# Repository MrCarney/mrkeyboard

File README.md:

# MrKeyboard

## Description
Ergogen 4.x generated low-profile backlit split keyboard with hot-swappable choc switches and per-key RGB LEDs.

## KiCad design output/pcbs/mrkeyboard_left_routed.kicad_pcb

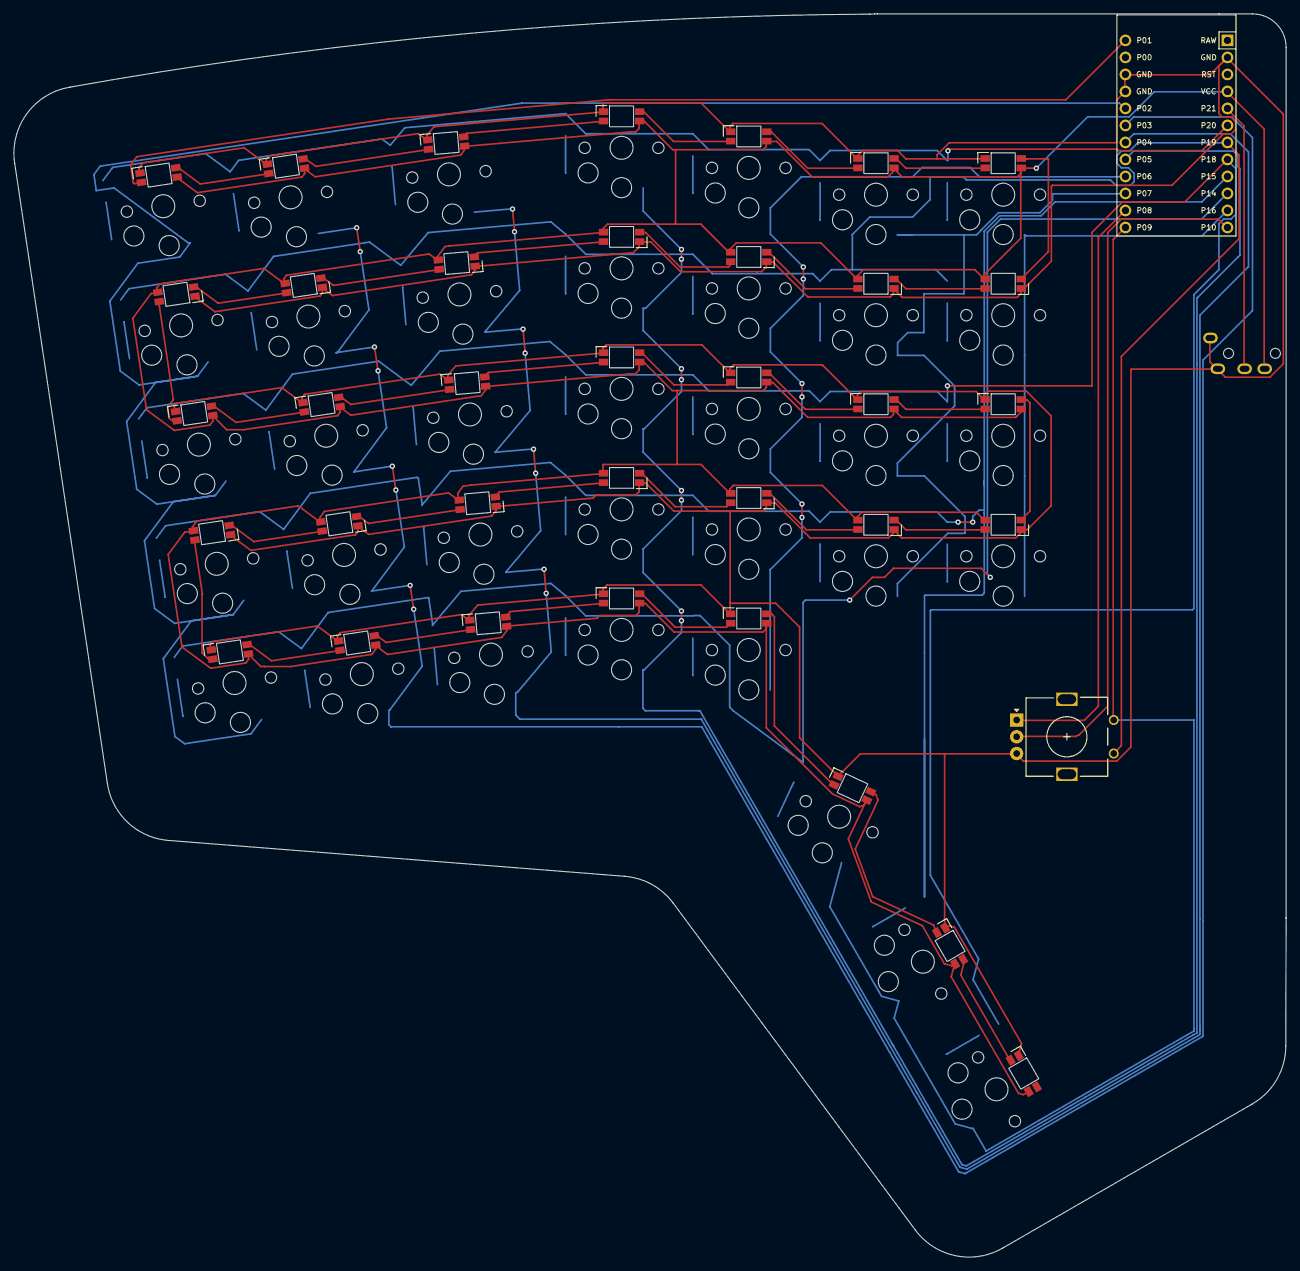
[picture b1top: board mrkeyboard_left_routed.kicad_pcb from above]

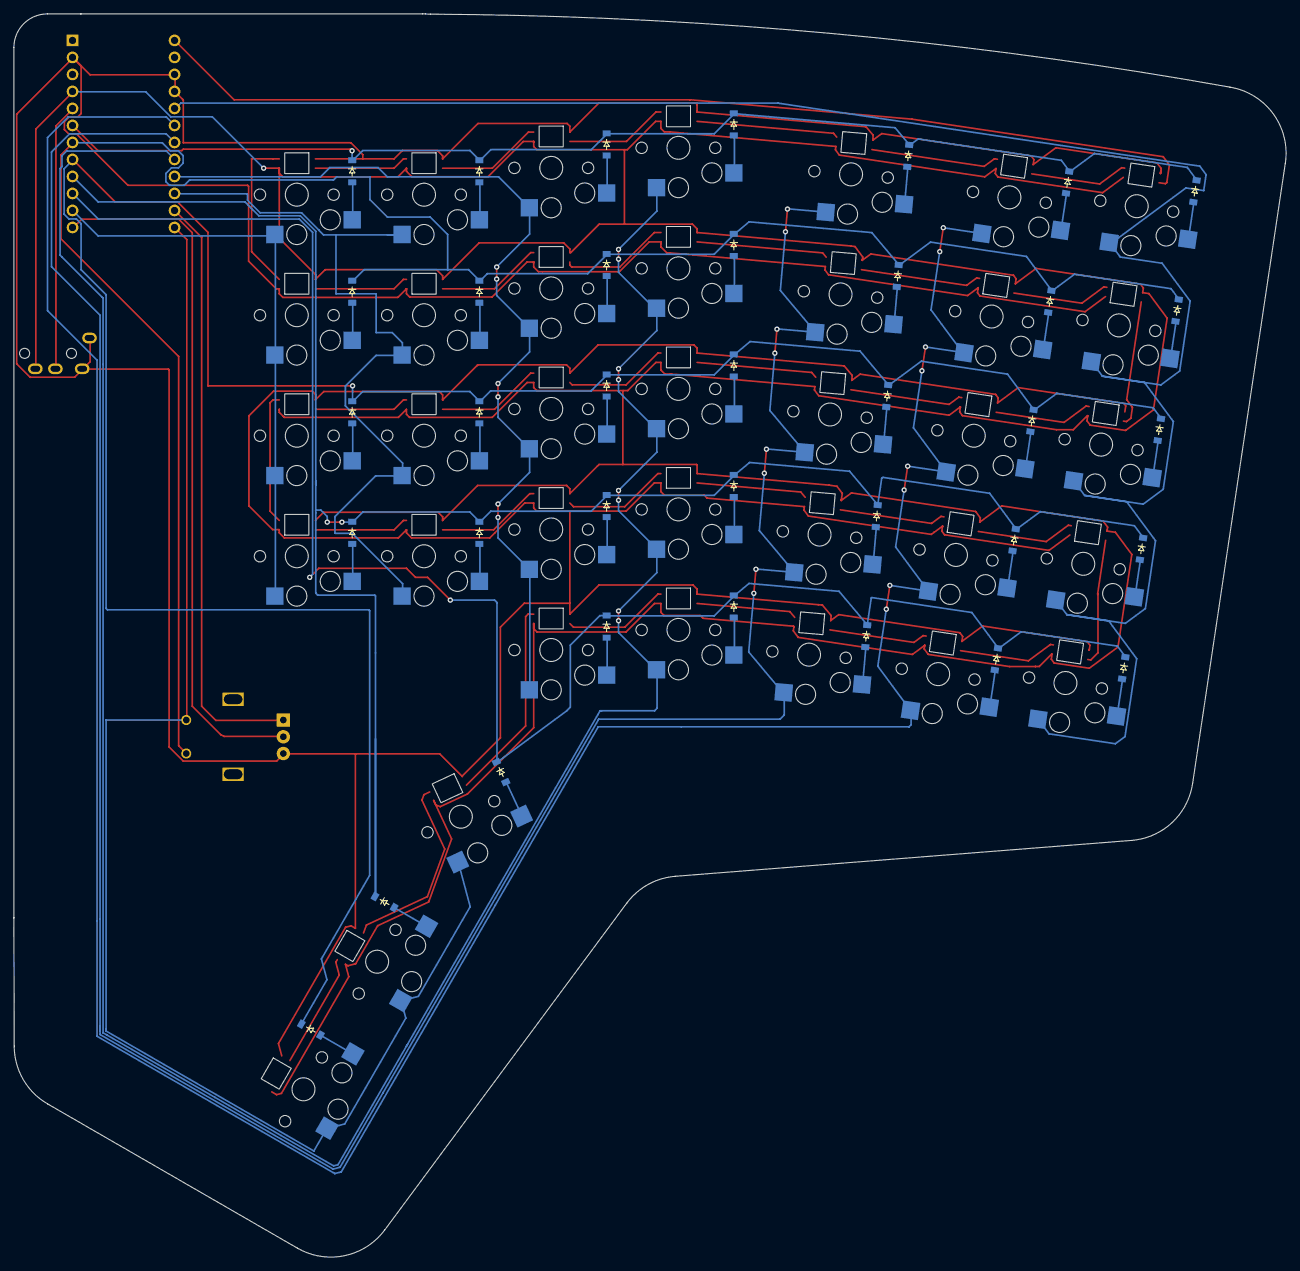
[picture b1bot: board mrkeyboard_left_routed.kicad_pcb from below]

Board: 2 copper layers, 190.0 x 185.7 mm, 111 parts (36 on the bottom side), 90 nets.

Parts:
D1, D2, D3, D4, D5, D6, D7, D8, D9, D10, D11, D12, D13, D14, D15, D16, D17, D18, D19, D20, D21, D22, D23, D24, D25, D26, D27, D28, D29, D30, D31, D32, D33, D34, D35, D36: ComboDiode
LED1, LED2, LED3, LED4, LED5, LED6, LED7, LED8, LED9, LED10, LED11, LED12, LED13, LED14, LED15, LED16, LED17, LED18, LED19, LED20, LED21, LED22, LED23, LED24, LED25, LED26, LED27, LED28, LED29, LED30, LED31, LED32, LED33, LED34, LED35, LED36: led_SK6812mini-e (underglowsingle-side)
MCU1: ProMicro
ROT1: rotary_encoder
S1, S2, S3, S4, S5, S6, S7, S8, S9, S10, S11, S12, S13, S14, S15, S16, S17, S18, S19, S20, S21, S22, S23, S24, S25, S26, S27, S28, S29, S30, S31, S32, S33, S34, S35, S36: PG1350
TRRS1: TRRS-PJ-320A-dual

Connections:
GND: LED1.3, LED2.3, LED3.3, LED4.3, LED5.3, LED6.3, LED7.3, LED8.3, LED9.3, LED10.3, LED11.3, LED12.3, LED13.3, LED14.3, LED15.3, LED16.3, LED17.3, LED18.3, LED19.3, LED20.3, LED21.3, LED22.3, LED23.3, LED24.3, LED25.3, LED26.3, LED27.3, LED28.3, LED29.3, LED30.3, LED31.3, LED32.3, LED33.3, LED34.3, LED35.3, LED36.3, MCU1.2, MCU1.15, MCU1.16, ROT1.B, TRRS1.1, TRRS1.2
L0102: LED5.2, LED10.4
L0203: LED10.2, LED15.4
L0304: LED15.2, LED20.4
L0405: LED20.2, LED25.4
L0506: LED25.2, LED29.4
L0607: LED29.2, LED33.4
L0714: LED32.4, LED33.2
L0815: LED3.4, LED4.2
L0908: LED4.4, LED9.2
L1009: LED9.4, LED14.2
L1110: LED14.4, LED19.2
L1211: LED19.4, LED24.2
L1312: LED24.4, LED28.2
L1413: LED28.4, LED32.2
L1516: LED3.2, LED8.4
L1617: LED8.2, LED13.4
L1718: LED13.2, LED18.4
L1819: LED18.2, LED23.4
L1920: LED23.2, LED27.4
L2021: LED27.2, LED31.4
L2128: LED30.4, LED31.2
L2229: LED1.4, LED2.2
L2322: LED2.4, LED7.2
L2423: LED7.4, LED12.2
L2524: LED12.4, LED17.2
L2625: LED17.4, LED22.2
L2726: LED22.4, LED26.2
L2827: LED26.4, LED30.2
L2930: LED1.2, LED6.4
L3031: LED6.2, LED11.4
L3132: LED11.2, LED16.4
L3233: LED16.2, LED21.4
L3334: LED21.2, LED34.4
L3435: LED34.2, LED35.4
L3536: LED35.2, LED36.4
P1: LED5.4, MCU1.13
P2: MCU1.17, S1.1, S2.1, S3.1, S4.1, S5.1
P3: MCU1.18, S6.1, S7.1, S8.1, S9.1, S10.1
P4: MCU1.19, S11.1, S12.1, S13.1, S14.1, S15.1
P5: MCU1.20, S16.1, S17.1, S18.1, S19.1, S20.1
P6: MCU1.21, S21.1, S22.1, S23.1, S24.1, S25.1
P7: MCU1.22, S26.1, S27.1, S28.1, S29.1
P8: MCU1.23, ROT1.A
P9: MCU1.24, ROT1.1, S34.1, S35.1, S36.1
P10: MCU1.12, ROT1.C
P14: D1.1, D6.1, D11.1, D16.1, D21.1, D34.1, MCU1.10
P15: D2.1, D7.1, D12.1, D17.1, D22.1, D26.1, D30.1, D35.1, MCU1.9
P16: MCU1.11, S30.1, S31.1, S32.1, S33.1
P18: D3.1, D8.1, D13.1, D18.1, D23.1, D27.1, D31.1, D36.1, MCU1.8
P19: D4.1, D9.1, D14.1, D19.1, D24.1, D28.1, D32.1, MCU1.7, ROT1.2
P20: D5.1, D10.1, D15.1, D20.1, D25.1, D29.1, D33.1, MCU1.6
P21: MCU1.5, TRRS1.3
VCC: LED1.1, LED2.1, LED3.1, LED4.1, LED5.1, LED6.1, LED7.1, LED8.1, LED9.1, LED10.1, LED11.1, LED12.1, LED13.1, LED14.1, LED15.1, LED16.1, LED17.1, LED18.1, LED19.1, LED20.1, LED21.1, LED22.1, LED23.1, LED24.1, LED25.1, LED26.1, LED27.1, LED28.1, LED29.1, LED30.1, LED31.1, LED32.1, LED33.1, LED34.1, LED35.1, LED36.1, MCU1.4, TRRS1.4
far_arrows: D1.2, S1.2
far_bottom: D2.2, S2.2
far_home: D3.2, S3.2
far_number: D5.2, S5.2
far_top: D4.2, S4.2
index_arrows: D21.2, S21.2
index_bottom: D22.2, S22.2
index_home: D23.2, S23.2
index_number: D25.2, S25.2
index_top: D24.2, S24.2
indexplus_bottom: D26.2, S26.2
indexplus_home: D27.2, S27.2
indexplus_number: D29.2, S29.2
indexplus_top: D28.2, S28.2
inside_bottom: D30.2, S30.2
inside_home: D31.2, S31.2
inside_number: D33.2, S33.2
inside_top: D32.2, S32.2
middle_arrows: D16.2, S16.2
middle_bottom: D17.2, S17.2
middle_home: D18.2, S18.2
middle_number: D20.2, S20.2
middle_top: D19.2, S19.2
pinkie_arrows: D6.2, S6.2
pinkie_bottom: D7.2, S7.2
pinkie_home: D8.2, S8.2
pinkie_number: D10.2, S10.2
pinkie_top: D9.2, S9.2
ring_arrows: D11.2, S11.2
ring_bottom: D12.2, S12.2
ring_home: D13.2, S13.2
ring_number: D15.2, S15.2
ring_top: D14.2, S14.2
tcenter_tbottom: D35.2, S35.2
tinside_tbottom: D34.2, S34.2
toutside_tbottom: D36.2, S36.2

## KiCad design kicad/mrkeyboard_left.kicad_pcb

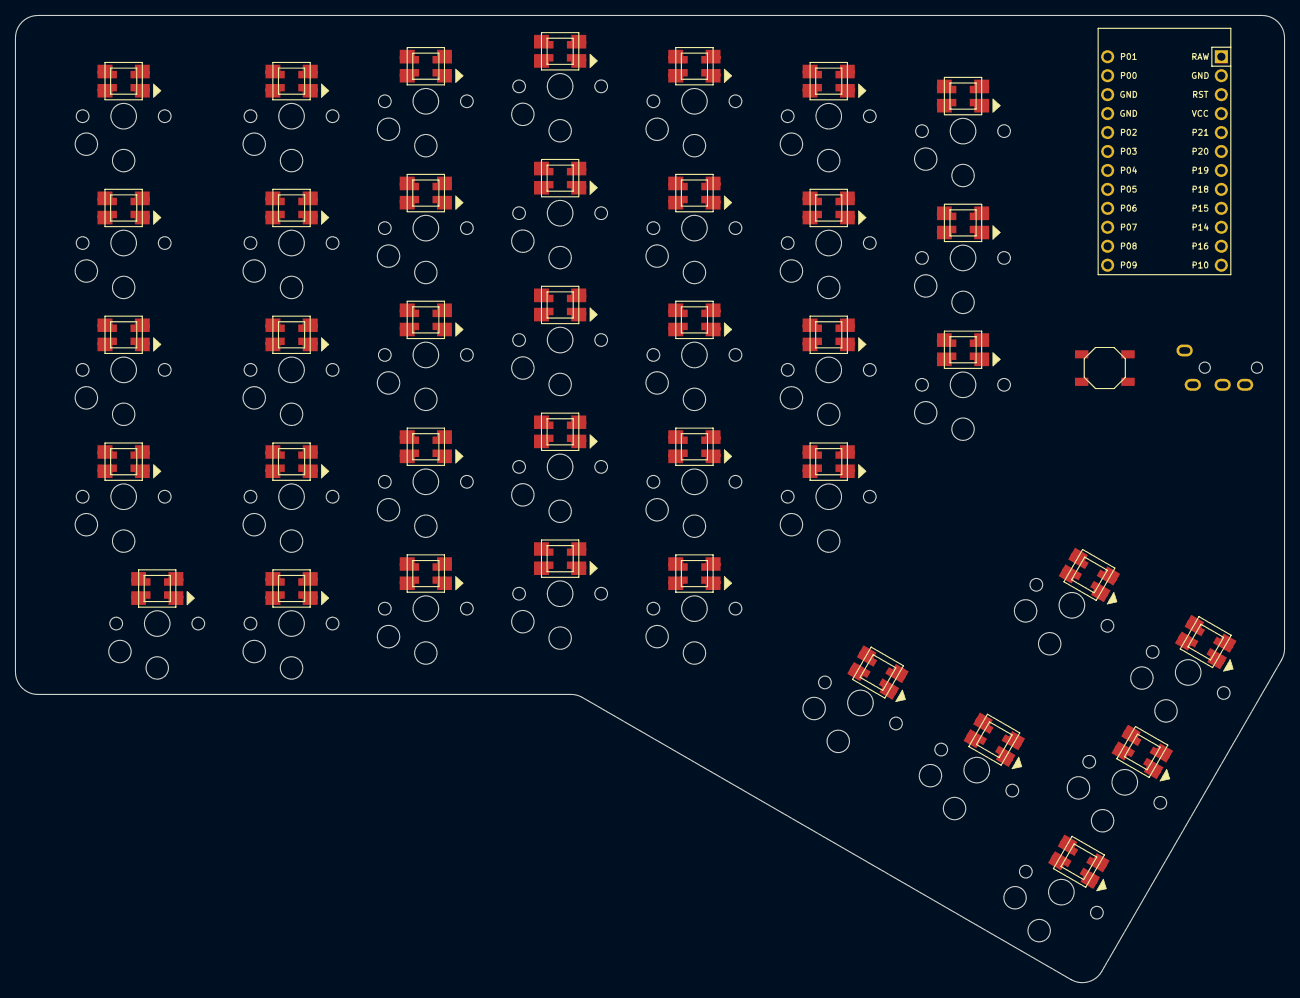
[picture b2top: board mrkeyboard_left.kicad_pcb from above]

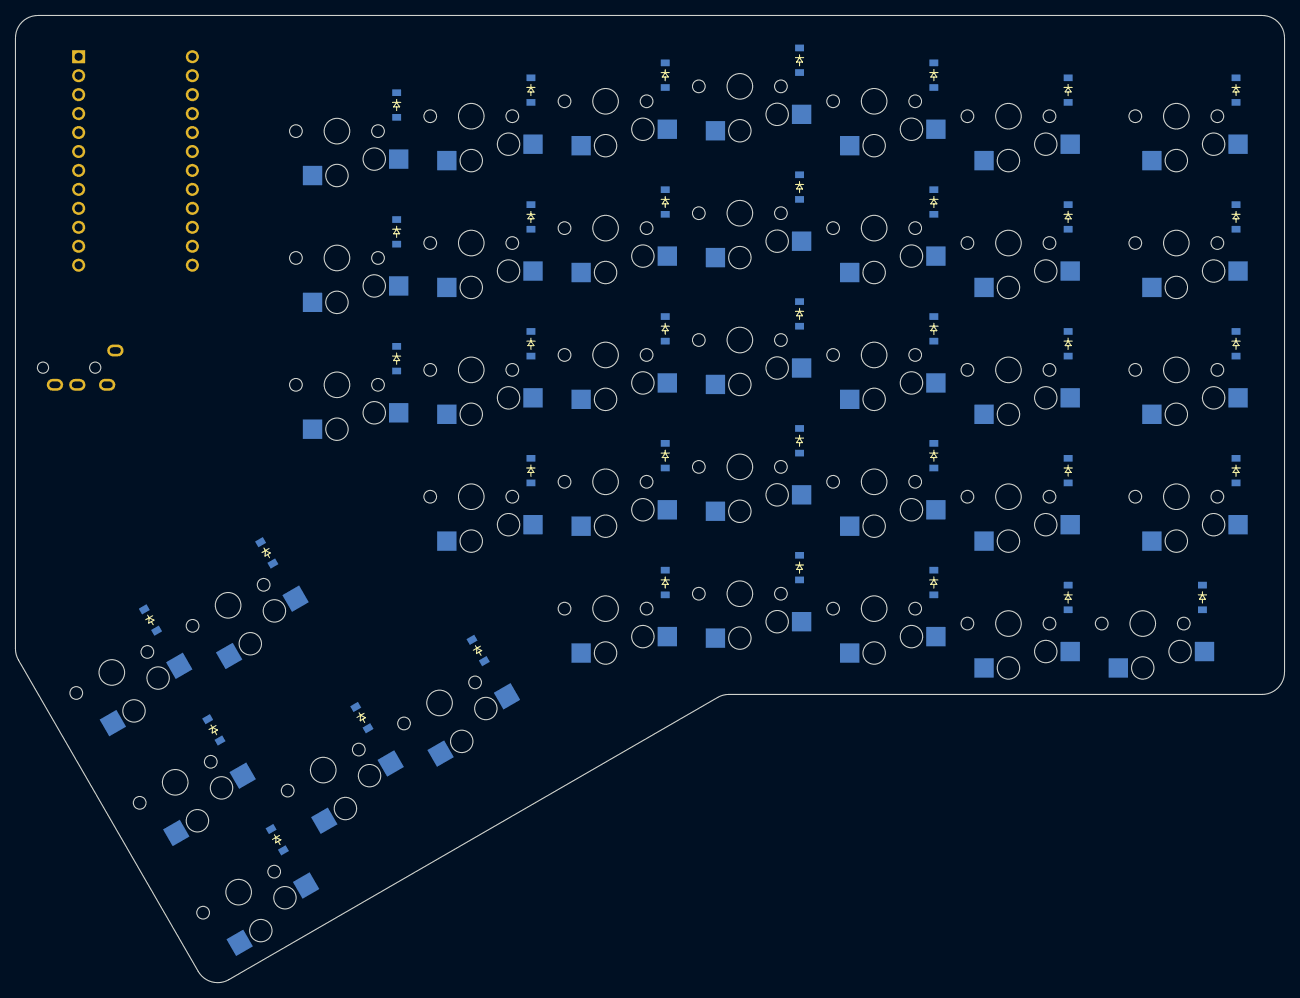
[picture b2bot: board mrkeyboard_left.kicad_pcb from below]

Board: 2 copper layers, 170.1 x 129.6 mm, 117 parts (38 on the bottom side), 131 nets, no tracks yet.

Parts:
B1: SW_TACT_ALPS_SKQGABE010
D1, D2, D3, D4, D5, D6, D7, D8, D9, D10, D11, D12, D13, D14, D15, D16, D17, D18, D19, D20, D21, D22, D23, D24, D25, D26, D27, D28, D29, D30, D31, D32, D33, D34, D35, D36, D37, D38: ComboDiode
LED1, LED2, LED3, LED4, LED5, LED6, LED7, LED8, LED9, LED10, LED11, LED12, LED13, LED14, LED15, LED16, LED17, LED18, LED19, LED20, LED21, LED22, LED23, LED24, LED25, LED26, LED27, LED28, LED29, LED30, LED31, LED32, LED33, LED34, LED35, LED36, LED37, LED38: WS2812B
MCU1: ProMicro
S1, S2, S3, S4, S5, S6, S7, S8, S9, S10, S11, S12, S13, S14, S15, S16, S17, S18, S19, S20, S21, S22, S23, S24, S25, S26, S27, S28, S29, S30, S31, S32, S33, S34, S35, S36, S37, S38: PG1350
TRRS1: TRRS-PJ-320A-dual

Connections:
GND: B1.2, LED1.3, LED1.33, LED2.3, LED2.33, LED3.3, LED3.33, LED4.3, LED4.33, LED5.3, LED5.33, LED6.3, LED6.33, LED7.3, LED7.33, LED8.3, LED8.33, LED9.3, LED9.33, LED10.3, LED10.33, LED11.3, LED11.33, LED12.3, LED12.33, LED13.3, LED13.33, LED14.3, LED14.33, LED15.3, LED15.33, LED16.3, LED16.33, LED17.3, LED17.33, LED18.3, LED18.33, LED19.3, LED19.33, LED20.3, LED20.33, LED21.3, LED21.33, LED22.3, LED22.33, LED23.3, LED23.33, LED24.3, LED24.33, LED25.3, LED25.33, LED26.3, LED26.33, LED27.3, LED27.33, LED28.3, LED28.33, LED29.3, LED29.33, LED30.3, LED30.33, LED31.3, LED31.33, LED32.3, LED32.33, LED33.3, LED33.33, LED34.3, LED34.33, LED35.3, LED35.33, LED36.3, LED36.33, LED37.3, LED37.33, LED38.3, LED38.33, MCU1.2, MCU1.15, MCU1.16, TRRS1.1, TRRS1.2
P2: D5.1, D10.1, D15.1, D20.1, D25.1, D29.1, D32.1, D33.1, MCU1.17
P3: D4.1, D9.1, D14.1, D19.1, D24.1, D28.1, D31.1, D34.1, MCU1.18
P4: D3.1, D8.1, D13.1, D18.1, D23.1, D27.1, D30.1, D36.1, MCU1.19
P5: D2.1, D7.1, D12.1, D17.1, D22.1, D26.1, D37.1, D38.1, MCU1.20
P6: D1.1, D6.1, D11.1, D16.1, D21.1, D35.1, MCU1.21
P7: MCU1.22, S33.2, S34.2, S36.2, S38.2
P10: MCU1.12, S30.2, S31.2, S32.2, S35.2, S37.2
P14: MCU1.10, S21.2, S22.2, S23.2, S24.2, S25.2
P15: MCU1.9, S16.2, S17.2, S18.2, S19.2, S20.2
P16: MCU1.11, S26.2, S27.2, S28.2, S29.2
P18: MCU1.8, S11.2, S12.2, S13.2, S14.2, S15.2
P19: MCU1.7, S6.2, S7.2, S8.2, S9.2, S10.2
P20: MCU1.6, S1.2, S2.2, S3.2, S4.2, S5.2
P21: MCU1.5, TRRS1.3
RST: B1.1, MCU1.3
VCC: LED1.1, LED1.11, LED2.1, LED2.11, LED3.1, LED3.11, LED4.1, LED4.11, LED5.1, LED5.11, LED6.1, LED6.11, LED7.1, LED7.11, LED8.1, LED8.11, LED9.1, LED9.11, LED10.1, LED10.11, LED11.1, LED11.11, LED12.1, LED12.11, LED13.1, LED13.11, LED14.1, LED14.11, LED15.1, LED15.11, LED16.1, LED16.11, LED17.1, LED17.11, LED18.1, LED18.11, LED19.1, LED19.11, LED20.1, LED20.11, LED21.1, LED21.11, LED22.1, LED22.11, LED23.1, LED23.11, LED24.1, LED24.11, LED25.1, LED25.11, LED26.1, LED26.11, LED27.1, LED27.11, LED28.1, LED28.11, LED29.1, LED29.11, LED30.1, LED30.11, LED31.1, LED31.11, LED32.1, LED32.11, LED33.1, LED33.11, LED34.1, LED34.11, LED35.1, LED35.11, LED36.1, LED36.11, LED37.1, LED37.11, LED38.1, LED38.11, MCU1.4, TRRS1.4
center_bottom: D34.2, S34.1
center_top: D35.2, S35.1
far_arrows: D1.2, S1.1
far_bottom: D2.2, S2.1
far_home: D3.2, S3.1
far_number: D5.2, S5.1
far_top: D4.2, S4.1
index_arrows: D21.2, S21.1
index_bottom: D22.2, S22.1
index_home: D23.2, S23.1
index_number: D25.2, S25.1
index_top: D24.2, S24.1
indexplus_bottom: D26.2, S26.1
indexplus_home: D27.2, S27.1
indexplus_number: D29.2, S29.1
indexplus_top: D28.2, S28.1
inside_bottom: D33.2, S33.1
inside_home: D30.2, S30.1
inside_number: D32.2, S32.1
inside_top: D31.2, S31.1
left_far_arrows_in: LED1.4, LED1.44
left_far_arrows_out: LED1.2, LED1.22
left_far_bottom_in: LED2.4, LED2.44
left_far_bottom_out: LED2.2, LED2.22
left_far_home_in: LED3.4, LED3.44
left_far_home_out: LED3.2, LED3.22
left_far_number_in: LED5.4, LED5.44
left_far_number_out: LED5.2, LED5.22
left_far_top_in: LED4.4, LED4.44
left_far_top_out: LED4.2, LED4.22
left_index_arrows_in: LED21.4, LED21.44
left_index_arrows_out: LED21.2, LED21.22
left_index_bottom_in: LED22.4, LED22.44
left_index_bottom_out: LED22.2, LED22.22
left_index_home_in: LED23.4, LED23.44
left_index_home_out: LED23.2, LED23.22
left_index_number_in: LED25.4, LED25.44
left_index_number_out: LED25.2, LED25.22
left_index_top_in: LED24.4, LED24.44
left_index_top_out: LED24.2, LED24.22
left_indexplus_bottom_in: LED26.4, LED26.44
left_indexplus_bottom_out: LED26.2, LED26.22
left_indexplus_home_in: LED27.4, LED27.44
left_indexplus_home_out: LED27.2, LED27.22
left_indexplus_number_in: LED29.4, LED29.44
left_indexplus_number_out: LED29.2, LED29.22
left_indexplus_top_in: LED28.4, LED28.44
left_indexplus_top_out: LED28.2, LED28.22
left_inside_home_in: LED30.4, LED30.44
left_inside_home_out: LED30.2, LED30.22
left_inside_number_in: LED32.4, LED32.44
left_inside_number_out: LED32.2, LED32.22
left_inside_top_in: LED31.4, LED31.44
left_inside_top_out: LED31.2, LED31.22
left_middle_arrows_in: LED16.4, LED16.44
left_middle_arrows_out: LED16.2, LED16.22
left_middle_bottom_in: LED17.4, LED17.44
left_middle_bottom_out: LED17.2, LED17.22
left_middle_home_in: LED18.4, LED18.44
left_middle_home_out: LED18.2, LED18.22
left_middle_number_in: LED20.4, LED20.44
left_middle_number_out: LED20.2, LED20.22
left_middle_top_in: LED19.4, LED19.44
left_middle_top_out: LED19.2, LED19.22
left_pinkie_arrows_in: LED6.4, LED6.44
left_pinkie_arrows_out: LED6.2, LED6.22
left_pinkie_bottom_in: LED7.4, LED7.44
left_pinkie_bottom_out: LED7.2, LED7.22
left_pinkie_home_in: LED8.4, LED8.44
left_pinkie_home_out: LED8.2, LED8.22
left_pinkie_number_in: LED10.4, LED10.44
left_pinkie_number_out: LED10.2, LED10.22
left_pinkie_top_in: LED9.4, LED9.44
left_pinkie_top_out: LED9.2, LED9.22
left_ring_arrows_in: LED11.4, LED11.44
left_ring_arrows_out: LED11.2, LED11.22
left_ring_bottom_in: LED12.4, LED12.44
left_ring_bottom_out: LED12.2, LED12.22
left_ring_home_in: LED13.4, LED13.44
left_ring_home_out: LED13.2, LED13.22
left_ring_number_in: LED15.4, LED15.44
left_ring_number_out: LED15.2, LED15.22
left_ring_top_in: LED14.4, LED14.44
left_ring_top_out: LED14.2, LED14.22
left_thumb_center_bottom_in: LED34.4, LED34.44
left_thumb_center_bottom_out: LED34.2, LED34.22
left_thumb_center_top_in: LED35.4, LED35.44
left_thumb_center_top_out: LED35.2, LED35.22
left_thumb_inside_bottom_in: LED33.4, LED33.44
left_thumb_inside_bottom_out: LED33.2, LED33.22
left_thumb_outside_bottom_in: LED36.4, LED36.44
left_thumb_outside_bottom_out: LED36.2, LED36.22
left_thumb_outside_middle_in: LED37.4, LED37.44
left_thumb_outside_middle_out: LED37.2, LED37.22
left_thumb_outside_top_in: LED38.4, LED38.44
left_thumb_outside_top_out: LED38.2, LED38.22
middle_arrows: D16.2, S16.1
middle_bottom: D17.2, S17.1
middle_home: D18.2, S18.1
middle_number: D20.2, S20.1
middle_top: D19.2, S19.1
outside_bottom: D36.2, S36.1
outside_middle: D37.2, S37.1
outside_top: D38.2, S38.1
pinkie_arrows: D6.2, S6.1
pinkie_bottom: D7.2, S7.1
pinkie_home: D8.2, S8.1
pinkie_number: D10.2, S10.1
pinkie_top: D9.2, S9.1
ring_arrows: D11.2, S11.1
ring_bottom: D12.2, S12.1
ring_home: D13.2, S13.1
ring_number: D15.2, S15.1
ring_top: D14.2, S14.1

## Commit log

2022-12-04 Initial commit.
2022-12-04 Added RGB and moved diode. Also moved VIAs.
2022-12-04 Fixed orientation of thumbcluster keys.
2022-12-04 Add Kicad PCB image
2022-12-18 Figured out math for outlines
2022-12-18 Placed PLC, TRRS, and reset button
2022-12-18 Fixed chocs and diode placements.
2022-12-19 Moving from raw.txt to left.txt. Starting to sort out routing.
2022-12-19 Rotate reset button.
2022-12-19 Update KiCad image.
2022-12-19 Touch to update image
2022-12-19 Rename left.txt to left.yaml
2022-12-19 Fixed footprints from/to
2022-12-19 Fixed row_nets
2022-12-20 Created master YAML file for both sides that generates two PCBs
2022-12-20 Force image cache update.
2022-12-20 Added RGBs back.
2022-12-20 Add KiCad files
2022-12-20 Removing old files.
2022-12-20 Adding .gitignore
2022-12-20 Cleaning up git repo
2022-12-21 Updated routing.
2024-07-26 Adjust layout after 3D printed testing of key placements
2024-08-02 First 3D print of left hand layout.
2024-08-02 Added right side
2024-08-04 Remove function keys. Curve the top.
2024-08-14 Remove reset button - it's included in the RP2040. Add RGB nets.
2024-08-17 Update images. Add non-standard footprints. Add routed PCB.
2024-08-17 Update README.md
    Add RGB
2024-08-19 Switched to 0xCB Helios
2024-08-19 Add 0xCB Helios
2024-08-21 Added roller encoder - it's not pinned yet
2024-09-25 Fix positions for encoders
2024-10-24 Adjusting pinouts. More work to do.
2025-07-16 Adding case plate and bottom.
2025-07-19 Fixed some syntax that wasn't being parsed. Changed the shape - got rid of giant circles. Added second row to thumb cluster. Added mounting holes. Moved encoders.
2025-07-20 Shift top row of thumb cluster up. Add a couple of mounting points for the test print. Make the hole for the roller encoder smaller so the test print can hold it.
2025-07-20 Move some keys around. Add some mounting holes for the test print.
2025-07-21 Move rotary encoder away from keys so thumb doesn't get pinched. Move roller encoder up. Move top stacked key on thumb cluster up so it's easier to feel. Re-order mounting holes to make more sense.
